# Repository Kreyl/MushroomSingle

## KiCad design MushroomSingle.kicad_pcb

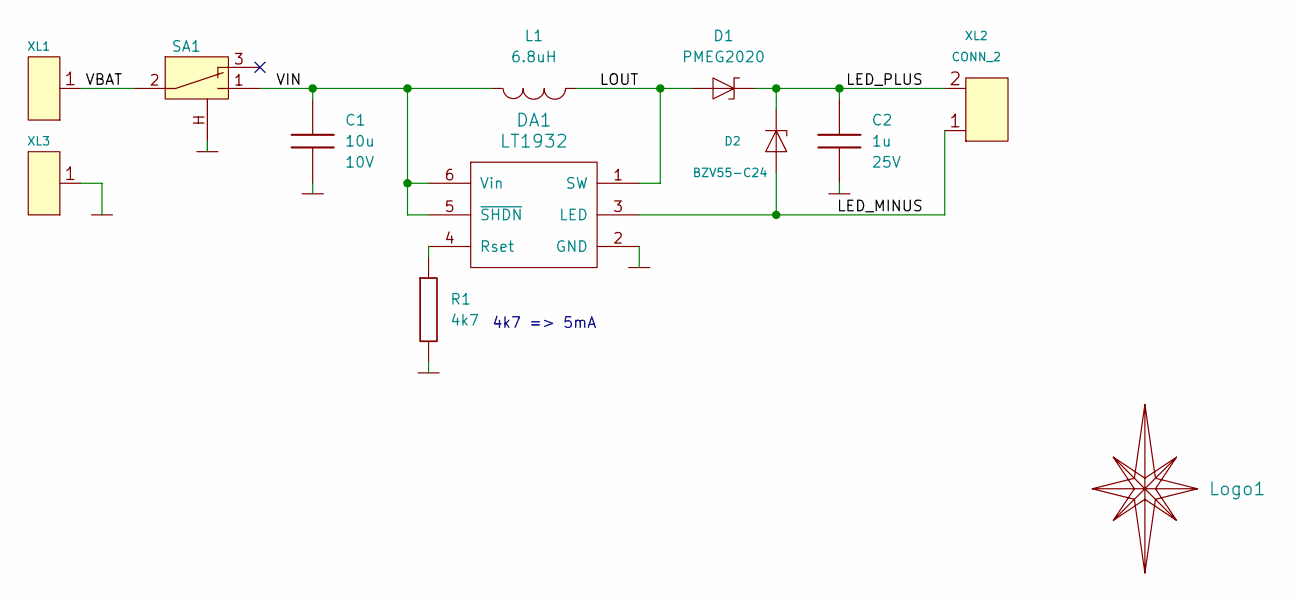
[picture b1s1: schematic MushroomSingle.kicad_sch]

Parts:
C1: 10u; CAP_0603; Tolerance 20%; Voltage 10V
C2: 1u; CAP_0603; Tolerance 20%; Voltage 25V
D1: PMEG2020; SOD323
D2: BZV55-C24; SOD80C
DA1: LT1932; SOT23-6
L1: 6.8uH; IND_1812; Tolerance 20%
Logo1: Logo; Ostranna_8x8
R1: 4k7; RES_0603; Tolerance 1%
SA1: SWITCH_1P2T_housing; SW_KLS7SS03_12D02
XL1, XL3: CONN_1; BAT_CONTACT_3X0d5
XL2: CONN_2; SLD_2_2D5_1mm

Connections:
/LED_MINUS: D2.A, DA1.3 (LED), XL2.1
/LED_PLUS: C2.1, D1.C, D2.C, XL2.2 (PM)
/LOUT: D1.A, DA1.1 (SW), L1.2
/VBAT: SA1.2, XL1.1
/VIN: C1.1, DA1.5 (~SHDN), DA1.6 (Vin), L1.1, SA1.1
GND: C1.2, C2.2, DA1.2 (GND), R1.2, SA1.H, XL3.1
unnamed: DA1.4 (Rset), R1.1

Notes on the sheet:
4k7 => 5mA

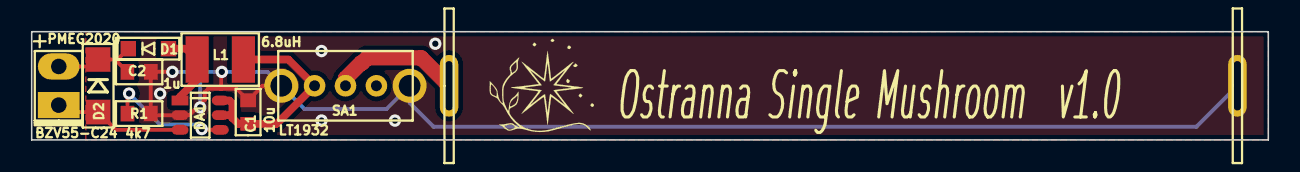
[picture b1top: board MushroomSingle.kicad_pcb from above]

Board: 2 copper layers, 80.0 x 7.0 mm, 12 parts (0 on the bottom side), 7 nets.

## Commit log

2021-06-23 Ach and PCB done
